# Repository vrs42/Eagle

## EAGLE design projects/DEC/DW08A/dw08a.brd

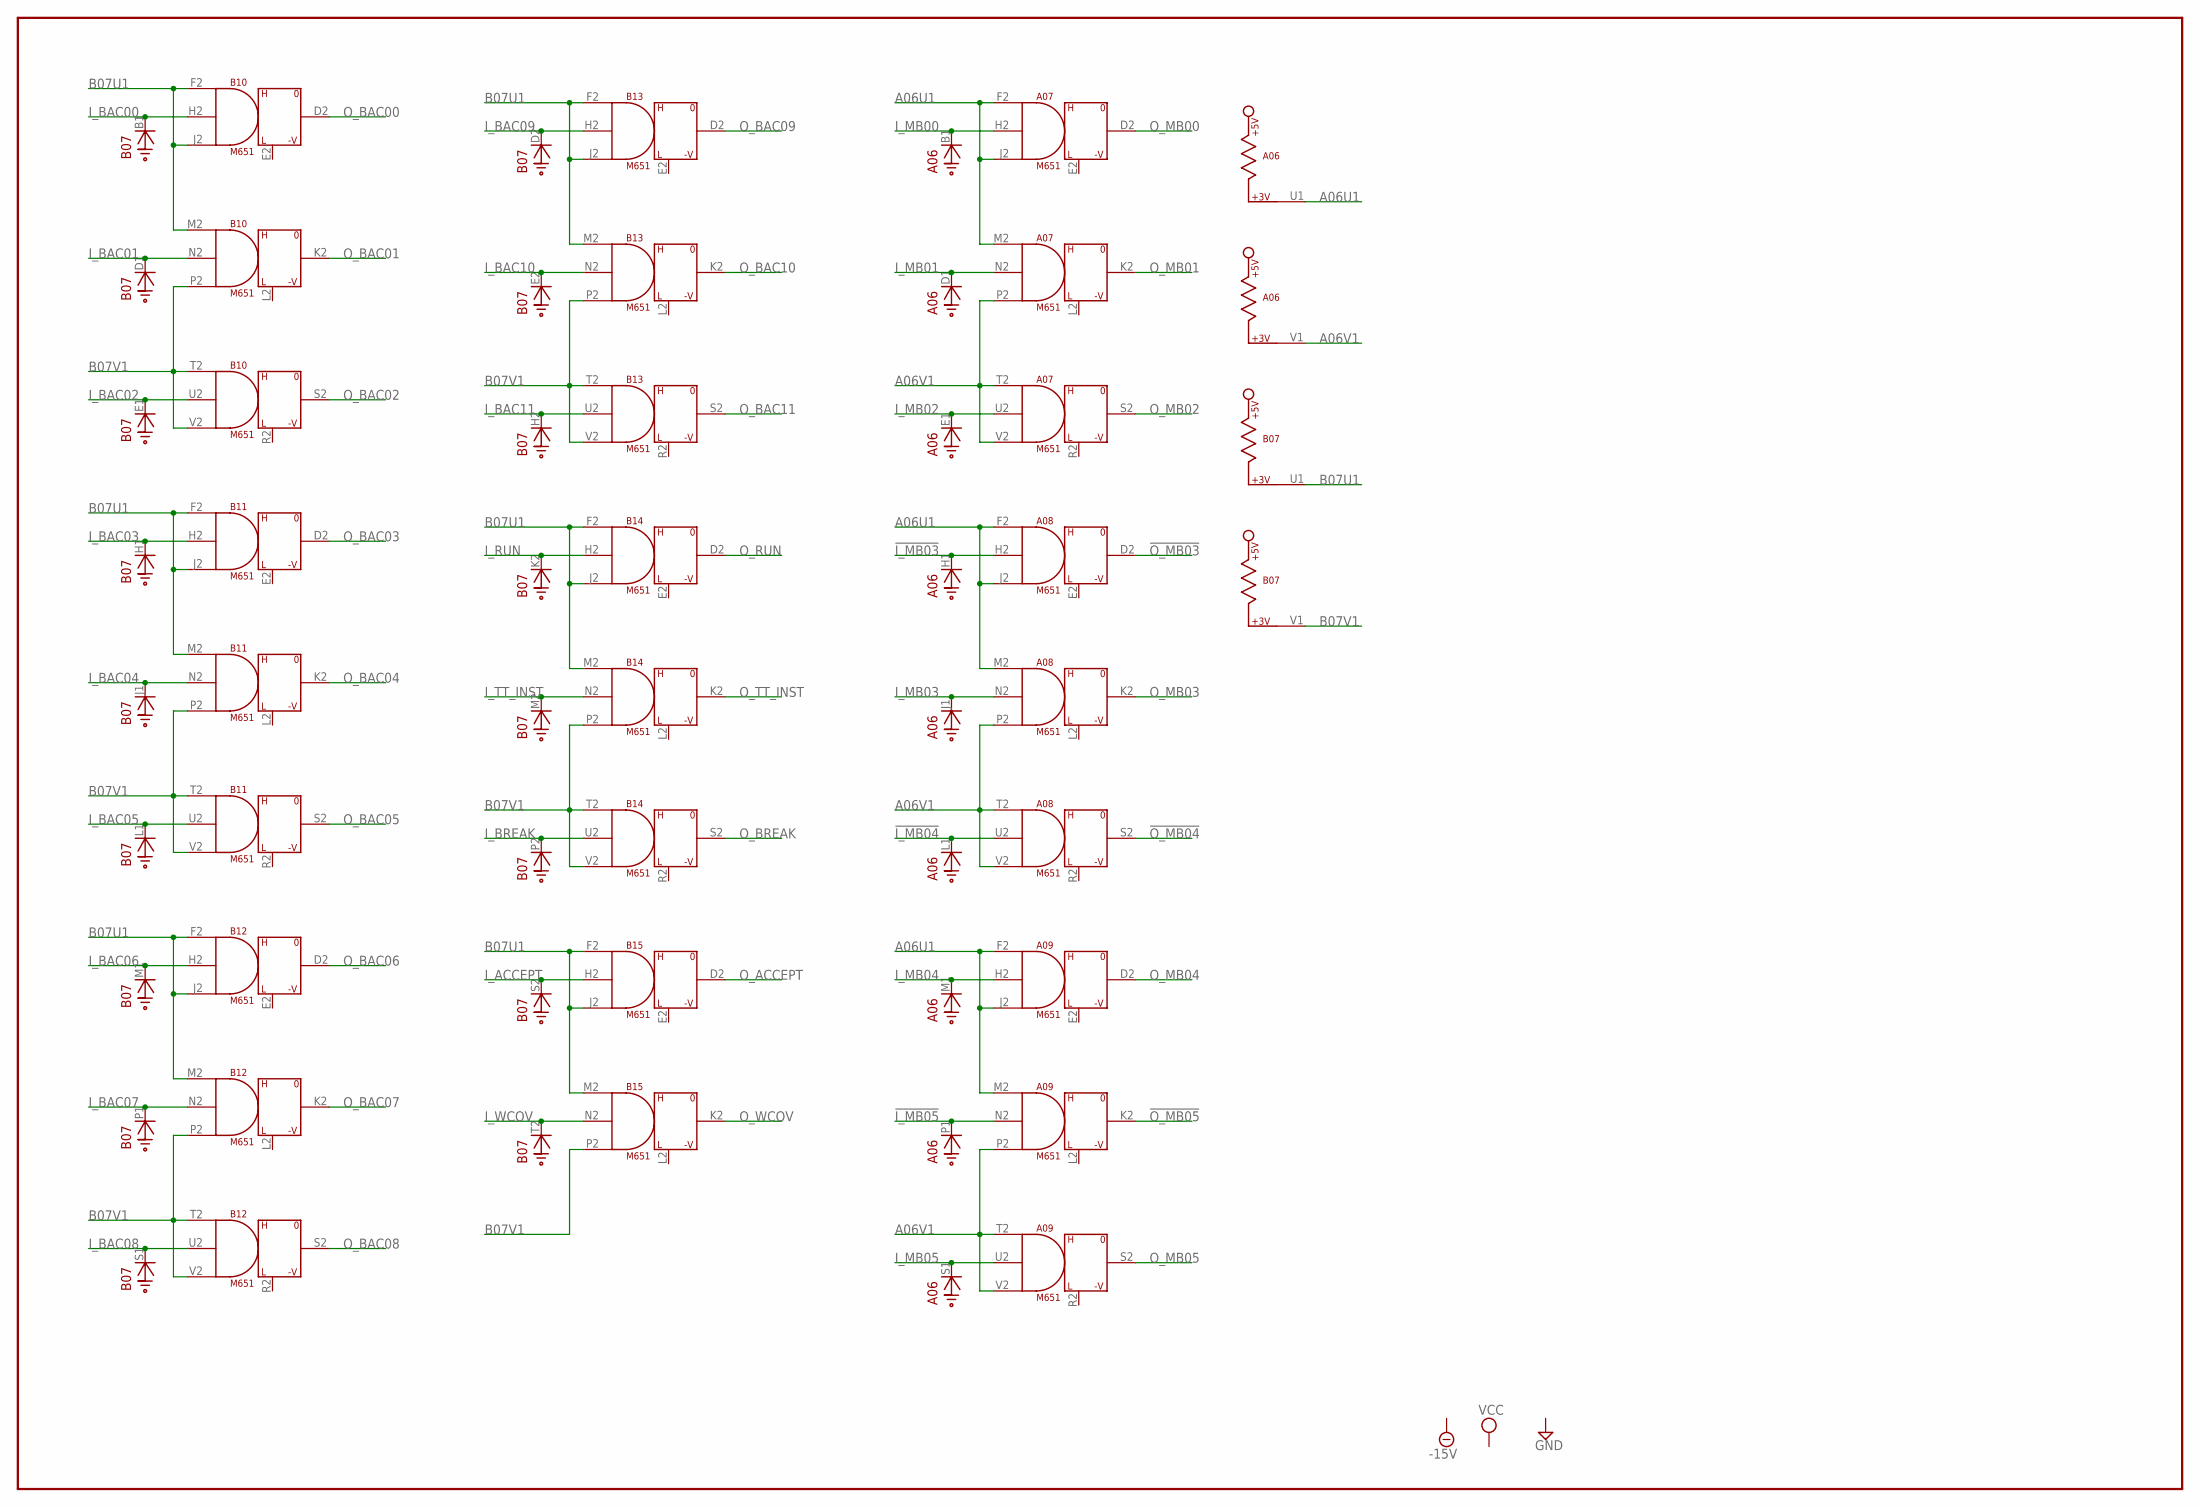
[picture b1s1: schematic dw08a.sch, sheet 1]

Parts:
A06: M907; H807
A07, A08, A09: M651; H807
B07: M907; H807
B10, B11, B12, B13, B14, B15: M651; H807

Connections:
!I_MB03: A06.H1 (CATHODE), A08.H2 (IN2); also elsewhere on the board
!I_MB04: A06.L1 (CATHODE), A08.U2 (IN2); also elsewhere on the board
!I_MB05: A06.P1 (CATHODE), A09.N2 (IN2); also elsewhere on the board
!O_MB03: A08.D2 (OUT); also elsewhere on the board
!O_MB04: A08.S2 (OUT); also elsewhere on the board
!O_MB05: A09.K2 (OUT); also elsewhere on the board
-15V: A07.B2 (-15V), A08.B2 (-15V), A09.B2 (-15V), B10.B2 (-15V), B11.B2 (-15V), B12.B2 (-15V), B13.B2 (-15V), B14.B2 (-15V), B15.B2 (-15V); also elsewhere on the board
A06U1: A06.U1, A07.F2 (IN1), A07.J2 (IN3), A07.M2 (IN1), A08.F2 (IN1), A08.J2 (IN3), A08.M2 (IN1), A09.F2 (IN1), A09.J2 (IN3), A09.M2 (IN1); also elsewhere on the board
A06V1: A06.V1, A07.P2 (IN3), A07.T2 (IN1), A07.V2 (IN3), A08.P2 (IN3), A08.T2 (IN1), A08.V2 (IN3), A09.P2 (IN3), A09.T2 (IN1), A09.V2 (IN3); also elsewhere on the board
B07U1: B07.U1, B10.F2 (IN1), B10.J2 (IN3), B10.M2 (IN1), B11.F2 (IN1), B11.J2 (IN3), B11.M2 (IN1), B12.F2 (IN1), B12.J2 (IN3), B12.M2 (IN1), B13.F2 (IN1), B13.J2 (IN3), B13.M2 (IN1), B14.F2 (IN1), B14.J2 (IN3), B14.M2 (IN1), B15.F2 (IN1), B15.J2 (IN3), B15.M2 (IN1); also elsewhere on the board
B07V1: B07.V1, B10.P2 (IN3), B10.T2 (IN1), B10.V2 (IN3), B11.P2 (IN3), B11.T2 (IN1), B11.V2 (IN3), B12.P2 (IN3), B12.T2 (IN1), B12.V2 (IN3), B13.P2 (IN3), B13.T2 (IN1), B13.V2 (IN3), B14.P2 (IN3), B14.T2 (IN1), B14.V2 (IN3), B15.P2 (IN3)
GND: A06.A1 (GND), A06.C1 (GND), A06.C2 (GND), A06.F1 (GND), A06.F2 (GND), A06.J2 (GND), A06.K1 (GND), A06.L2 (GND), A06.N1 (GND), A06.N2 (GND), A06.R1 (GND), A06.R2 (GND), A06.T1 (GND), A06.U2 (GND), A07.C2 (GND), A08.C2 (GND), A09.C2 (GND), B07.A1 (GND), B07.C1 (GND), B07.C2 (GND), B07.F1 (GND), B07.F2 (GND), B07.J2 (GND), B07.K1 (GND), B07.L2 (GND), B07.N1 (GND), B07.N2 (GND), B07.R1 (GND), B07.R2 (GND), B07.T1 (GND), B07.U2 (GND), B10.C2 (GND), B11.C2 (GND), B12.C2 (GND), B13.C2 (GND), B14.C2 (GND), B15.C2 (GND); also elsewhere on the board
I_ACCEPT: B07.S2 (CATHODE), B15.H2 (IN2); also elsewhere on the board
I_BAC00: B07.B1 (CATHODE), B10.H2 (IN2); also elsewhere on the board
I_BAC01: B07.D1 (CATHODE), B10.N2 (IN2); also elsewhere on the board
I_BAC02: B07.E1 (CATHODE), B10.U2 (IN2); also elsewhere on the board
I_BAC03: B07.H1 (CATHODE), B11.H2 (IN2); also elsewhere on the board
I_BAC04: B07.J1 (CATHODE), B11.N2 (IN2); also elsewhere on the board
I_BAC05: B07.L1 (CATHODE), B11.U2 (IN2); also elsewhere on the board
I_BAC06: B07.M1 (CATHODE), B12.H2 (IN2); also elsewhere on the board
I_BAC07: B07.P1 (CATHODE), B12.N2 (IN2); also elsewhere on the board
I_BAC08: B07.S1 (CATHODE), B12.U2 (IN2); also elsewhere on the board
I_BAC09: B07.D2 (CATHODE), B13.H2 (IN2); also elsewhere on the board
I_BAC10: B07.E2 (CATHODE), B13.N2 (IN2); also elsewhere on the board
I_BAC11: B07.H2 (CATHODE), B13.U2 (IN2); also elsewhere on the board
I_BREAK: B07.P2 (CATHODE), B14.U2 (IN2); also elsewhere on the board
I_MB00: A06.B1 (CATHODE), A07.H2 (IN2); also elsewhere on the board
I_MB01: A06.D1 (CATHODE), A07.N2 (IN2); also elsewhere on the board
I_MB02: A06.E1 (CATHODE), A07.U2 (IN2); also elsewhere on the board
I_MB03: A06.J1 (CATHODE), A08.N2 (IN2); also elsewhere on the board
I_MB04: A06.M1 (CATHODE), A09.H2 (IN2); also elsewhere on the board
I_MB05: A06.S1 (CATHODE), A09.U2 (IN2); also elsewhere on the board
I_RUN: B07.K2 (CATHODE), B14.H2 (IN2); also elsewhere on the board
I_TT_INST: B07.M2 (CATHODE), B14.N2 (IN2); also elsewhere on the board
I_WCOV: B07.T2 (CATHODE), B15.N2 (IN2); also elsewhere on the board
O_ACCEPT: B15.D2 (OUT); also elsewhere on the board
O_BAC00: B10.D2 (OUT); also elsewhere on the board
O_BAC01: B10.K2 (OUT); also elsewhere on the board
O_BAC02: B10.S2 (OUT); also elsewhere on the board
O_BAC03: B11.D2 (OUT); also elsewhere on the board
O_BAC04: B11.K2 (OUT); also elsewhere on the board
O_BAC05: B11.S2 (OUT); also elsewhere on the board
O_BAC06: B12.D2 (OUT); also elsewhere on the board
O_BAC07: B12.K2 (OUT); also elsewhere on the board
O_BAC08: B12.S2 (OUT); also elsewhere on the board
O_BAC09: B13.D2 (OUT); also elsewhere on the board
O_BAC10: B13.K2 (OUT); also elsewhere on the board
O_BAC11: B13.S2 (OUT); also elsewhere on the board
O_BREAK: B14.S2 (OUT); also elsewhere on the board
O_MB00: A07.D2 (OUT); also elsewhere on the board
O_MB01: A07.K2 (OUT); also elsewhere on the board
O_MB02: A07.S2 (OUT); also elsewhere on the board
O_MB03: A08.K2 (OUT); also elsewhere on the board
O_MB04: A09.D2 (OUT); also elsewhere on the board
O_MB05: A09.S2 (OUT); also elsewhere on the board
O_RUN: B14.D2 (OUT); also elsewhere on the board
O_TT_INST: B14.K2 (OUT); also elsewhere on the board
O_WCOV: B15.K2 (OUT); also elsewhere on the board
VCC: A06.A2 (VCC), A07.A2 (VCC), A08.A2 (VCC), A09.A2 (VCC), B07.A2 (VCC), B10.A2 (VCC), B11.A2 (VCC), B12.A2 (VCC), B13.A2 (VCC), B14.A2 (VCC), B15.A2 (VCC); also elsewhere on the board

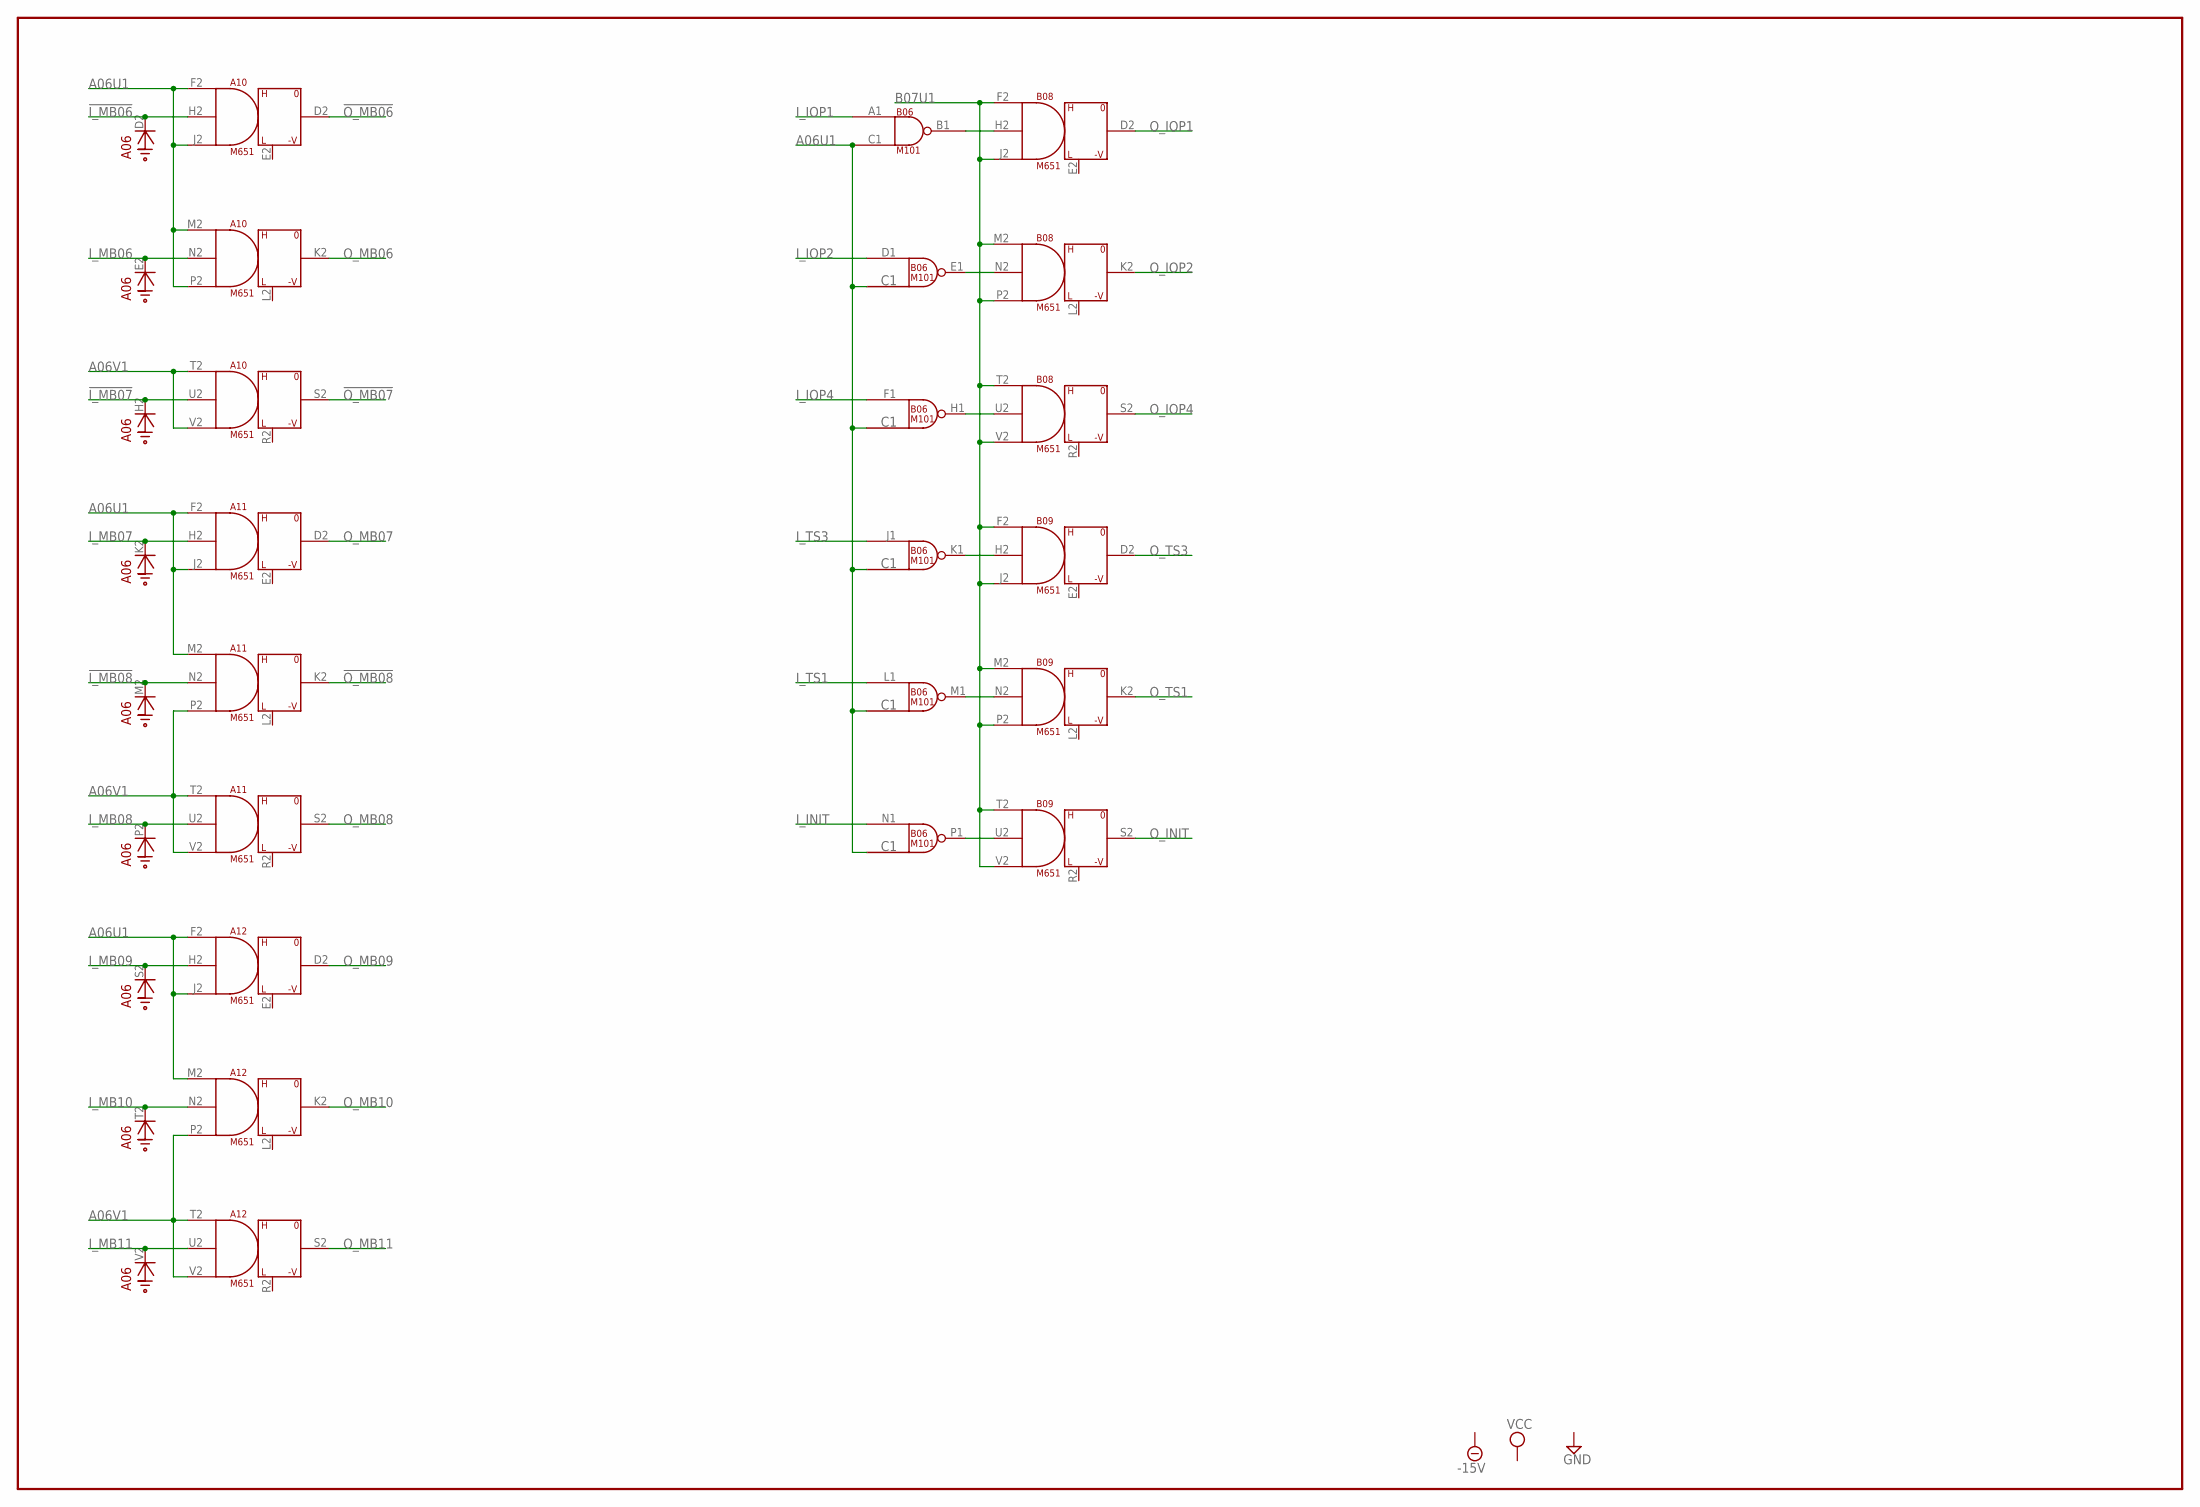
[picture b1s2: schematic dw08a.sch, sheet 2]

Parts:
A06: M907; H807
A10, A11, A12: M651; H807
B06: M101; H807
B08, B09: M651; H807

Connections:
!I_MB06: A06.D2 (CATHODE), A10.H2 (IN2); also elsewhere on the board
!I_MB07: A06.H2 (CATHODE), A10.U2 (IN2); also elsewhere on the board
!I_MB08: A06.M2 (CATHODE), A11.N2 (IN2); also elsewhere on the board
!O_MB06: A10.D2 (OUT); also elsewhere on the board
!O_MB07: A10.S2 (OUT); also elsewhere on the board
!O_MB08: A11.K2 (OUT); also elsewhere on the board
-15V: A10.B2 (-15V), A11.B2 (-15V), A12.B2 (-15V), B08.B2 (-15V), B09.B2 (-15V); also elsewhere on the board
A06U1: A10.F2 (IN1), A10.J2 (IN3), A10.M2 (IN1), A10.P2 (IN3), A11.F2 (IN1), A11.J2 (IN3), A11.M2 (IN1), A12.F2 (IN1), A12.J2 (IN3), A12.M2 (IN1), B06.C1 (IN2); also elsewhere on the board
A06V1: A10.T2 (IN1), A10.V2 (IN3), A11.P2 (IN3), A11.T2 (IN1), A11.V2 (IN3), A12.P2 (IN3), A12.T2 (IN1), A12.V2 (IN3); also elsewhere on the board
B07U1: B08.F2 (IN1), B08.J2 (IN3), B08.M2 (IN1), B08.P2 (IN3), B08.T2 (IN1), B08.V2 (IN3), B09.F2 (IN1), B09.J2 (IN3), B09.M2 (IN1), B09.P2 (IN3), B09.T2 (IN1), B09.V2 (IN3); also elsewhere on the board
GND: A06.A1 (GND), A06.C1 (GND), A06.C2 (GND), A06.F1 (GND), A06.F2 (GND), A06.J2 (GND), A06.K1 (GND), A06.L2 (GND), A06.N1 (GND), A06.N2 (GND), A06.R1 (GND), A06.R2 (GND), A06.T1 (GND), A06.U2 (GND), A10.C2 (GND), A11.C2 (GND), A12.C2 (GND), B06.C2 (GND), B06.T1 (GND), B08.C2 (GND), B09.C2 (GND); also elsewhere on the board
I_INIT: B06.N1 (IN); also elsewhere on the board
I_IOP1: B06.A1 (IN1); also elsewhere on the board
I_IOP2: B06.D1 (IN); also elsewhere on the board
I_IOP4: B06.F1 (IN); also elsewhere on the board
I_MB06: A06.E2 (CATHODE), A10.N2 (IN2); also elsewhere on the board
I_MB07: A06.K2 (CATHODE), A11.H2 (IN2); also elsewhere on the board
I_MB08: A06.P2 (CATHODE), A11.U2 (IN2); also elsewhere on the board
I_MB09: A06.S2 (CATHODE), A12.H2 (IN2); also elsewhere on the board
I_MB10: A06.T2 (CATHODE), A12.N2 (IN2); also elsewhere on the board
I_MB11: A06.V2 (CATHODE), A12.U2 (IN2); also elsewhere on the board
I_TS1: B06.L1 (IN); also elsewhere on the board
I_TS3: B06.J1 (IN); also elsewhere on the board
unnamed: B06.B1 (OUT), B08.H2 (IN2)
unnamed: B06.E1 (OUT), B08.N2 (IN2)
unnamed: B06.H1 (OUT), B08.U2 (IN2)
unnamed: B06.K1 (OUT), B09.H2 (IN2)
unnamed: B06.M1 (OUT), B09.N2 (IN2)
unnamed: B06.P1 (OUT), B09.U2 (IN2)
O_INIT: B09.S2 (OUT); also elsewhere on the board
O_IOP1: B08.D2 (OUT); also elsewhere on the board
O_IOP2: B08.K2 (OUT); also elsewhere on the board
O_IOP4: B08.S2 (OUT); also elsewhere on the board
O_MB06: A10.K2 (OUT); also elsewhere on the board
O_MB07: A11.D2 (OUT); also elsewhere on the board
O_MB08: A11.S2 (OUT); also elsewhere on the board
O_MB09: A12.D2 (OUT); also elsewhere on the board
O_MB10: A12.K2 (OUT); also elsewhere on the board
O_MB11: A12.S2 (OUT); also elsewhere on the board
O_TS1: B09.K2 (OUT); also elsewhere on the board
O_TS3: B09.D2 (OUT); also elsewhere on the board
VCC: A06.A2 (VCC), A10.A2 (VCC), A11.A2 (VCC), A12.A2 (VCC), B06.A2 (VCC), B08.A2 (VCC), B09.A2 (VCC); also elsewhere on the board

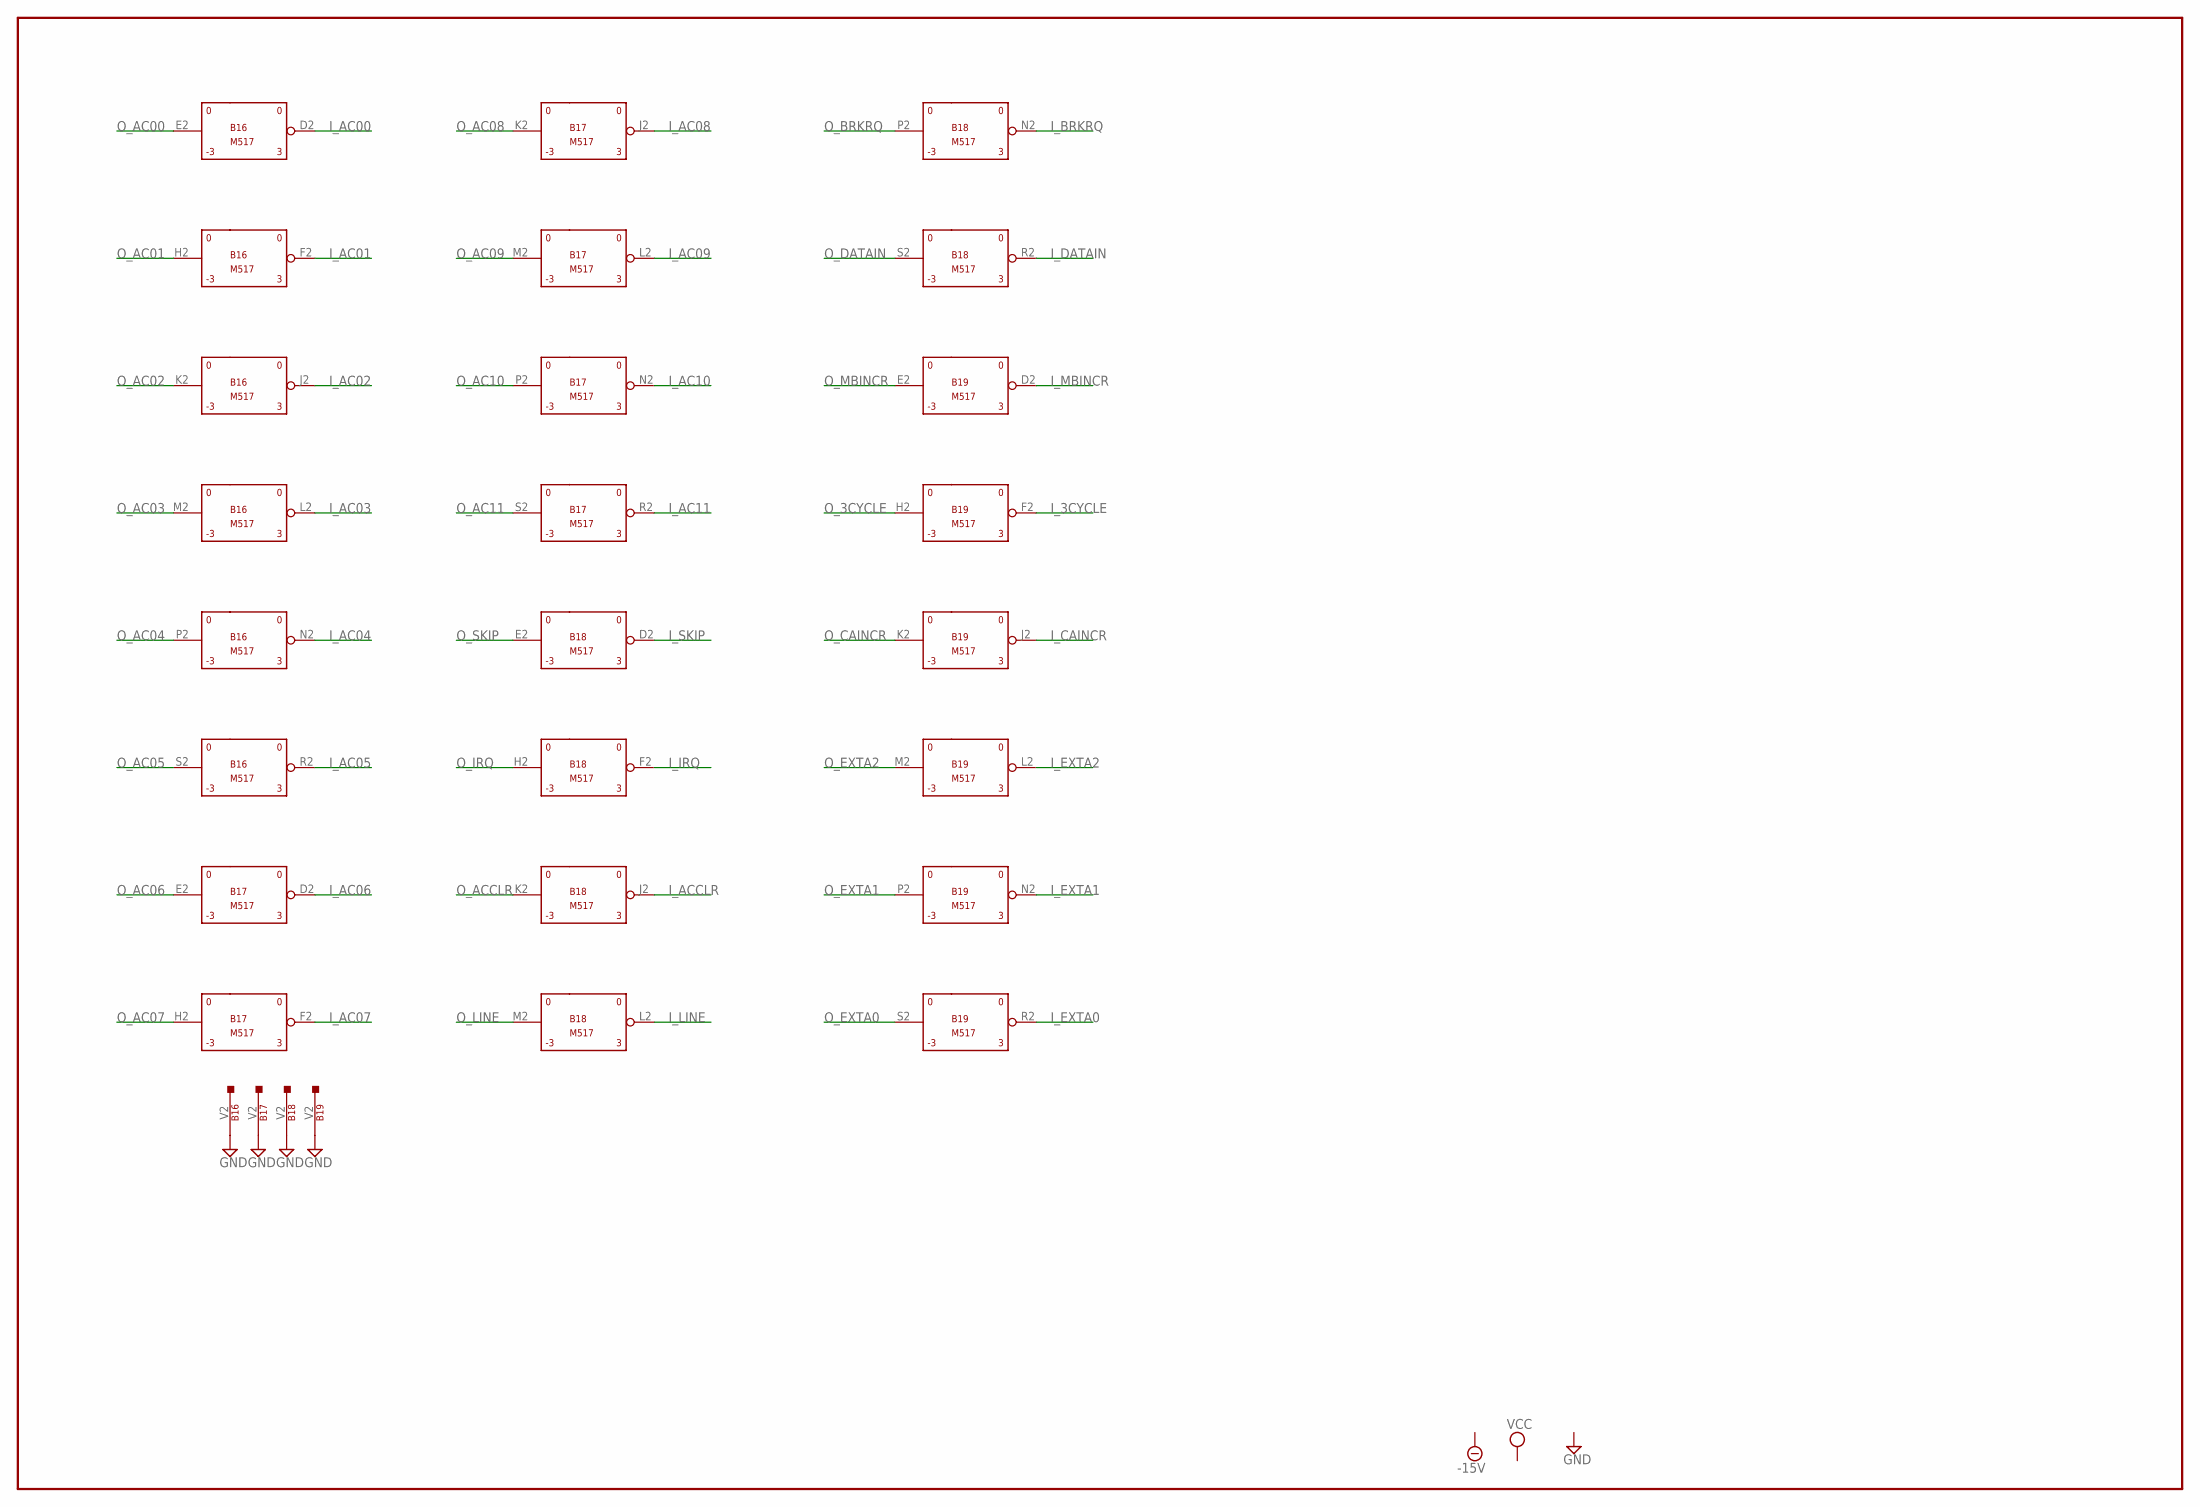
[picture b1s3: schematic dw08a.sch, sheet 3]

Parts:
B16, B17, B18, B19: M517; H807

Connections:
-15V: B16.B2 (-15V), B17.B2 (-15V), B18.B2 (-15V), B19.B2 (-15V); also elsewhere on the board
GND: B16.C2 (GND), B16.T2 (GND), B16.U2 (GND), B16.V2, B17.C2 (GND), B17.T2 (GND), B17.U2 (GND), B17.V2, B18.C2 (GND), B18.T2 (GND), B18.U2 (GND), B18.V2, B19.C2 (GND), B19.T2 (GND), B19.U2 (GND), B19.V2; also elsewhere on the board
I_3CYCLE: B19.F2 (OUT); also elsewhere on the board
I_AC00: B16.D2 (OUT); also elsewhere on the board
I_AC01: B16.F2 (OUT); also elsewhere on the board
I_AC02: B16.J2 (OUT); also elsewhere on the board
I_AC03: B16.L2 (OUT); also elsewhere on the board
I_AC04: B16.N2 (OUT); also elsewhere on the board
I_AC05: B16.R2 (OUT); also elsewhere on the board
I_AC06: B17.D2 (OUT); also elsewhere on the board
I_AC07: B17.F2 (OUT); also elsewhere on the board
I_AC08: B17.J2 (OUT); also elsewhere on the board
I_AC09: B17.L2 (OUT); also elsewhere on the board
I_AC10: B17.N2 (OUT); also elsewhere on the board
I_AC11: B17.R2 (OUT); also elsewhere on the board
I_ACCLR: B18.J2 (OUT); also elsewhere on the board
I_BRKRQ: B18.N2 (OUT); also elsewhere on the board
I_CAINCR: B19.J2 (OUT); also elsewhere on the board
I_DATAIN: B18.R2 (OUT); also elsewhere on the board
I_EXTA0: B19.R2 (OUT); also elsewhere on the board
I_EXTA1: B19.N2 (OUT); also elsewhere on the board
I_EXTA2: B19.L2 (OUT); also elsewhere on the board
I_IRQ: B18.F2 (OUT); also elsewhere on the board
I_LINE: B18.L2 (OUT); also elsewhere on the board
I_MBINCR: B19.D2 (OUT); also elsewhere on the board
I_SKIP: B18.D2 (OUT); also elsewhere on the board
O_3CYCLE: B19.H2 (IN); also elsewhere on the board
O_AC00: B16.E2 (IN); also elsewhere on the board
O_AC01: B16.H2 (IN); also elsewhere on the board
O_AC02: B16.K2 (IN); also elsewhere on the board
O_AC03: B16.M2 (IN); also elsewhere on the board
O_AC04: B16.P2 (IN); also elsewhere on the board
O_AC05: B16.S2 (IN); also elsewhere on the board
O_AC06: B17.E2 (IN); also elsewhere on the board
O_AC07: B17.H2 (IN); also elsewhere on the board
O_AC08: B17.K2 (IN); also elsewhere on the board
O_AC09: B17.M2 (IN); also elsewhere on the board
O_AC10: B17.P2 (IN); also elsewhere on the board
O_AC11: B17.S2 (IN); also elsewhere on the board
O_ACCLR: B18.K2 (IN); also elsewhere on the board
O_BRKRQ: B18.P2 (IN); also elsewhere on the board
O_CAINCR: B19.K2 (IN); also elsewhere on the board
O_DATAIN: B18.S2 (IN); also elsewhere on the board
O_EXTA0: B19.S2 (IN); also elsewhere on the board
O_EXTA1: B19.P2 (IN); also elsewhere on the board
O_EXTA2: B19.M2 (IN); also elsewhere on the board
O_IRQ: B18.H2 (IN); also elsewhere on the board
O_LINE: B18.M2 (IN); also elsewhere on the board
O_MBINCR: B19.E2 (IN); also elsewhere on the board
O_SKIP: B18.E2 (IN); also elsewhere on the board
VCC: B16.A2 (VCC), B17.A2 (VCC), B18.A2 (VCC), B19.A2 (VCC); also elsewhere on the board

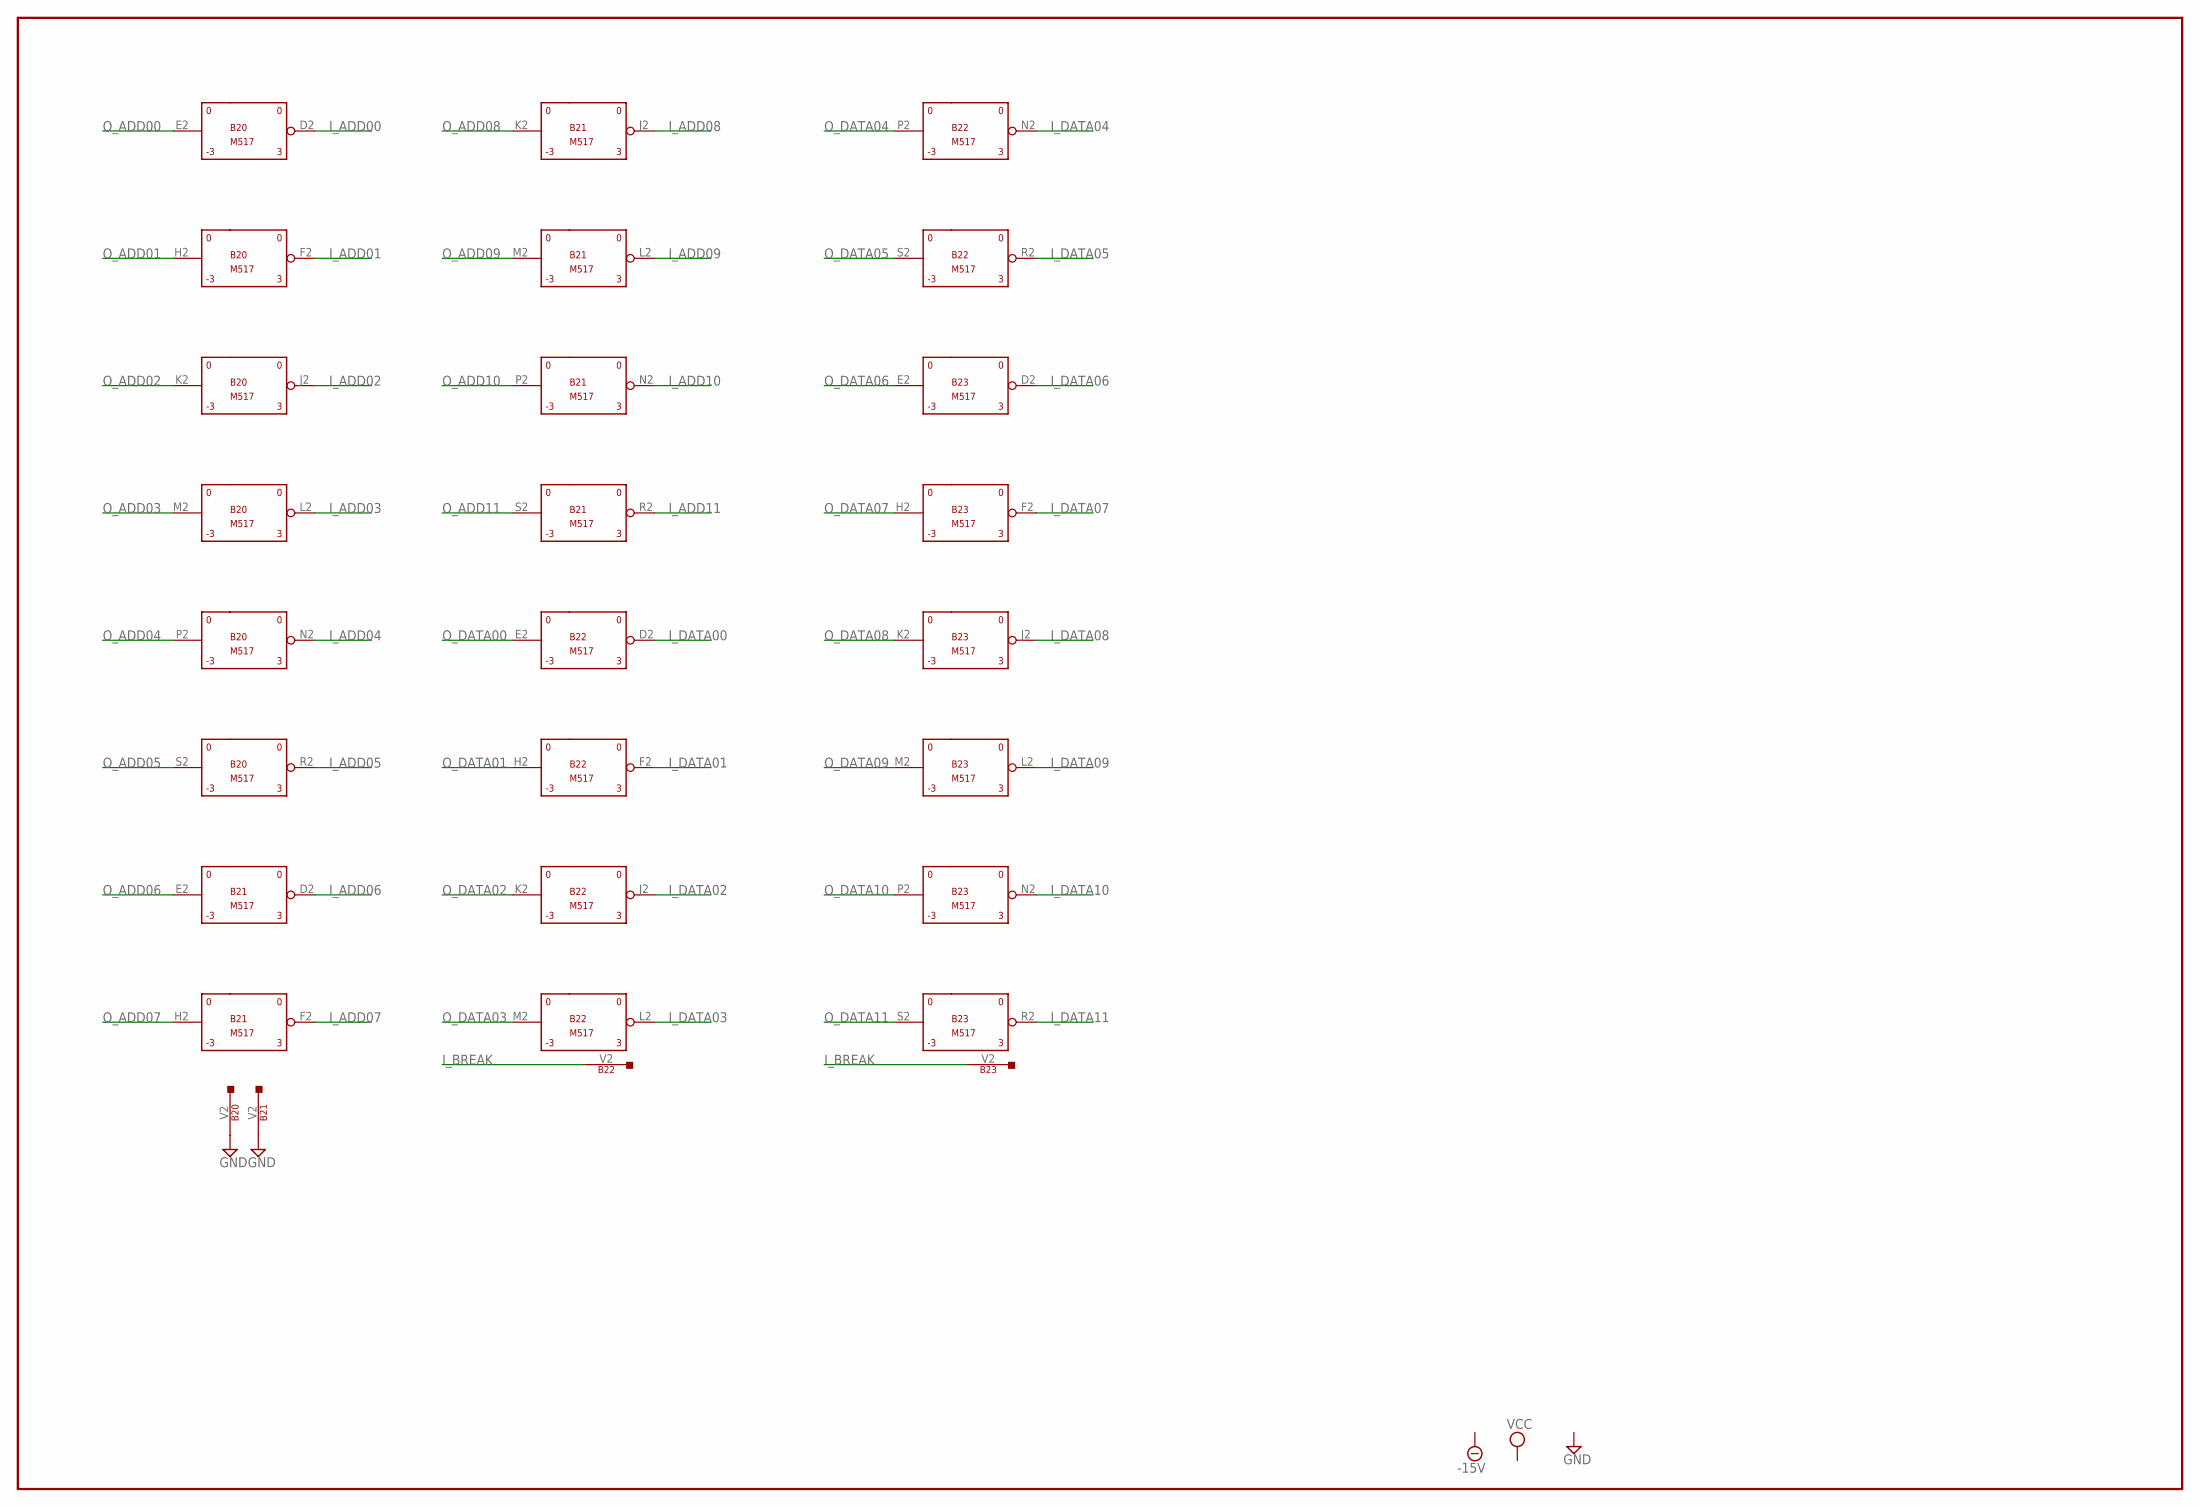
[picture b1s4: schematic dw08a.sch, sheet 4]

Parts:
B20, B21, B22, B23: M517; H807

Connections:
-15V: B20.B2 (-15V), B21.B2 (-15V), B22.B2 (-15V), B23.B2 (-15V); also elsewhere on the board
GND: B20.C2 (GND), B20.T2 (GND), B20.U2 (GND), B20.V2, B21.C2 (GND), B21.T2 (GND), B21.U2 (GND), B21.V2, B22.C2 (GND), B22.T2 (GND), B22.U2 (GND), B23.C2 (GND), B23.T2 (GND), B23.U2 (GND); also elsewhere on the board
I_ADD00: B20.D2 (OUT); also elsewhere on the board
I_ADD01: B20.F2 (OUT); also elsewhere on the board
I_ADD02: B20.J2 (OUT); also elsewhere on the board
I_ADD03: B20.L2 (OUT); also elsewhere on the board
I_ADD04: B20.N2 (OUT); also elsewhere on the board
I_ADD05: B20.R2 (OUT); also elsewhere on the board
I_ADD06: B21.D2 (OUT); also elsewhere on the board
I_ADD07: B21.F2 (OUT); also elsewhere on the board
I_ADD08: B21.J2 (OUT); also elsewhere on the board
I_ADD09: B21.L2 (OUT); also elsewhere on the board
I_ADD10: B21.N2 (OUT); also elsewhere on the board
I_ADD11: B21.R2 (OUT); also elsewhere on the board
I_BREAK: B22.V2, B23.V2; also elsewhere on the board
I_DATA00: B22.D2 (OUT); also elsewhere on the board
I_DATA01: B22.F2 (OUT); also elsewhere on the board
I_DATA02: B22.J2 (OUT); also elsewhere on the board
I_DATA03: B22.L2 (OUT); also elsewhere on the board
I_DATA04: B22.N2 (OUT); also elsewhere on the board
I_DATA05: B22.R2 (OUT); also elsewhere on the board
I_DATA06: B23.D2 (OUT); also elsewhere on the board
I_DATA07: B23.F2 (OUT); also elsewhere on the board
I_DATA08: B23.J2 (OUT); also elsewhere on the board
I_DATA09: B23.L2 (OUT); also elsewhere on the board
I_DATA10: B23.N2 (OUT); also elsewhere on the board
I_DATA11: B23.R2 (OUT); also elsewhere on the board
O_ADD00: B20.E2 (IN); also elsewhere on the board
O_ADD01: B20.H2 (IN); also elsewhere on the board
O_ADD02: B20.K2 (IN); also elsewhere on the board
O_ADD03: B20.M2 (IN); also elsewhere on the board
O_ADD04: B20.P2 (IN); also elsewhere on the board
O_ADD05: B20.S2 (IN); also elsewhere on the board
O_ADD06: B21.E2 (IN); also elsewhere on the board
O_ADD07: B21.H2 (IN); also elsewhere on the board
O_ADD08: B21.K2 (IN); also elsewhere on the board
O_ADD09: B21.M2 (IN); also elsewhere on the board
O_ADD10: B21.P2 (IN); also elsewhere on the board
O_ADD11: B21.S2 (IN); also elsewhere on the board
O_DATA00: B22.E2 (IN); also elsewhere on the board
O_DATA01: B22.H2 (IN); also elsewhere on the board
O_DATA02: B22.K2 (IN); also elsewhere on the board
O_DATA03: B22.M2 (IN); also elsewhere on the board
O_DATA04: B22.P2 (IN); also elsewhere on the board
O_DATA05: B22.S2 (IN); also elsewhere on the board
O_DATA06: B23.E2 (IN); also elsewhere on the board
O_DATA07: B23.H2 (IN); also elsewhere on the board
O_DATA08: B23.K2 (IN); also elsewhere on the board
O_DATA09: B23.M2 (IN); also elsewhere on the board
O_DATA10: B23.P2 (IN); also elsewhere on the board
O_DATA11: B23.S2 (IN); also elsewhere on the board
VCC: B20.A2 (VCC), B21.A2 (VCC), B22.A2 (VCC), B23.A2 (VCC); also elsewhere on the board
